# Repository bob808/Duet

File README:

# The Sweet Silence! 3D Printer Controller design files repository.

Sweeet Silence is a Duet2 Wifi spinoff, using tmc2228 drivers, mounted on the back of the pcb for better 
cooling (heatsinks on top pf pcb). Uses the same ATSAM4E8E processor. Output stage has been completely redone,
and includes full protection suite from the datasheet (ferrite beads/varistors and caps on BRA/BRB).
There's 2x MAX31865 chips on board, you can use it directly with PT100/1000 sensors. There's also options
for 4/3/2 wire setups.
The driver control should be the same from Maestro.
There's E2/E3 extra UART connections for external drivers.
Few pins from 2x25 header are different, and debugging led is gone. Everything else should be the same.

Will update later on with more details. I found all parts at TME/Farnell. 
Firmware needs to be modified to account for correct pin numbers.
Ah, and max31865 is to be bitbanged. No hardware SPI in that area.

The recommended firmware is DC42's branch of the RepRapFirmware:
https://github.com/dc42/RepRapFirmware

Based on :
Duet 2 Wifi 
Design by Tony Lock and David Crocker
More info:
https://www.duet3d.com/
LICENSE: see the LICENSE file in the repository

Developed in KiCAD: http://www.kicad-pcb.org/display/KICAD/KiCad+EDA+Software+Suite

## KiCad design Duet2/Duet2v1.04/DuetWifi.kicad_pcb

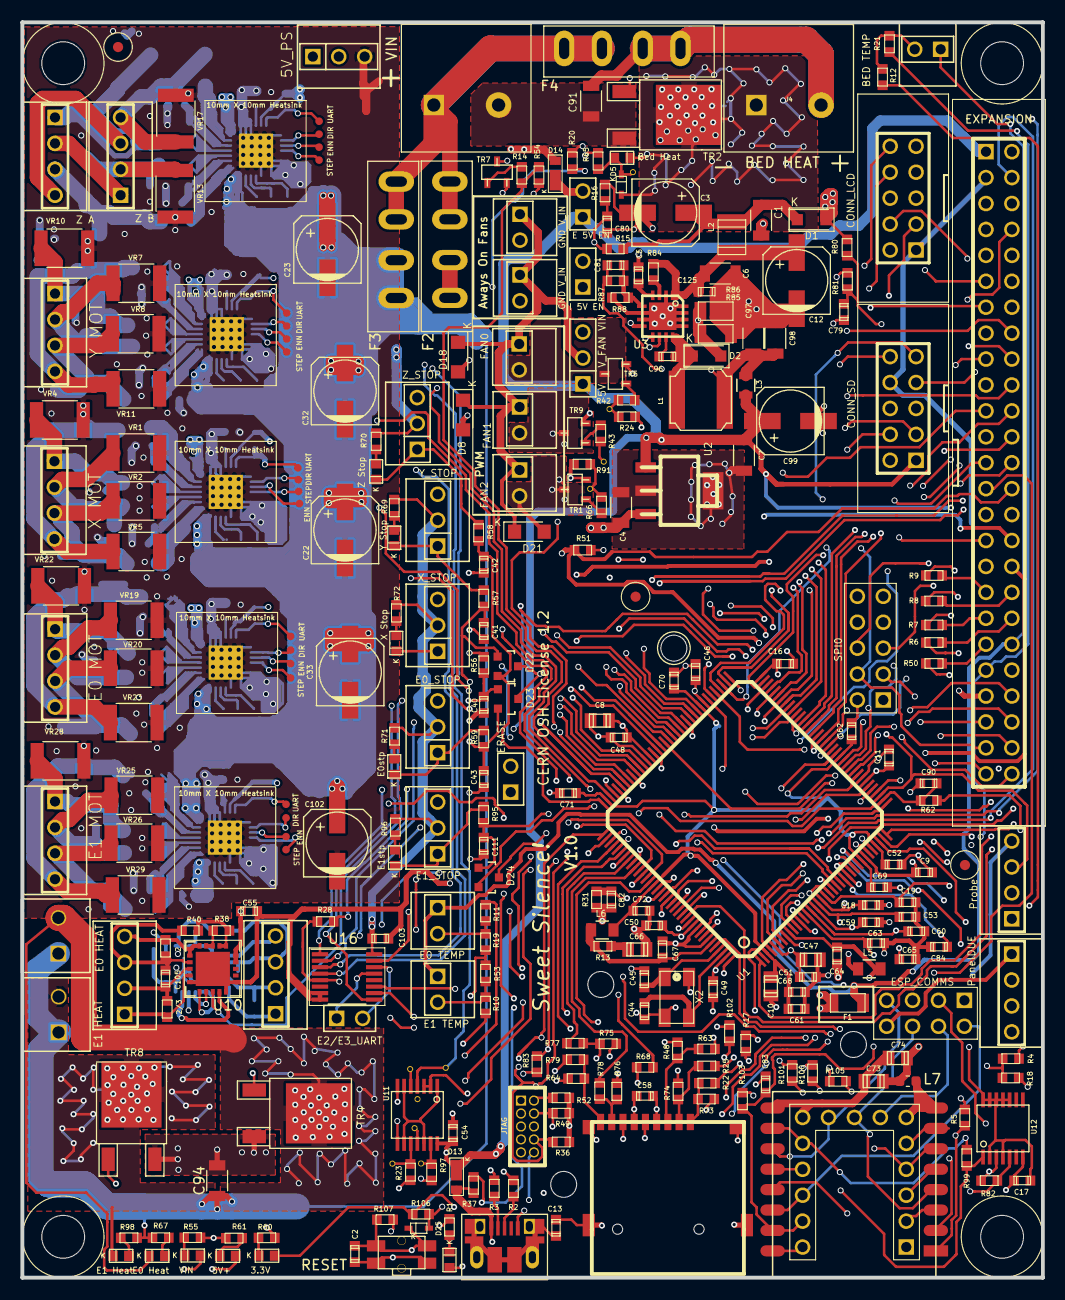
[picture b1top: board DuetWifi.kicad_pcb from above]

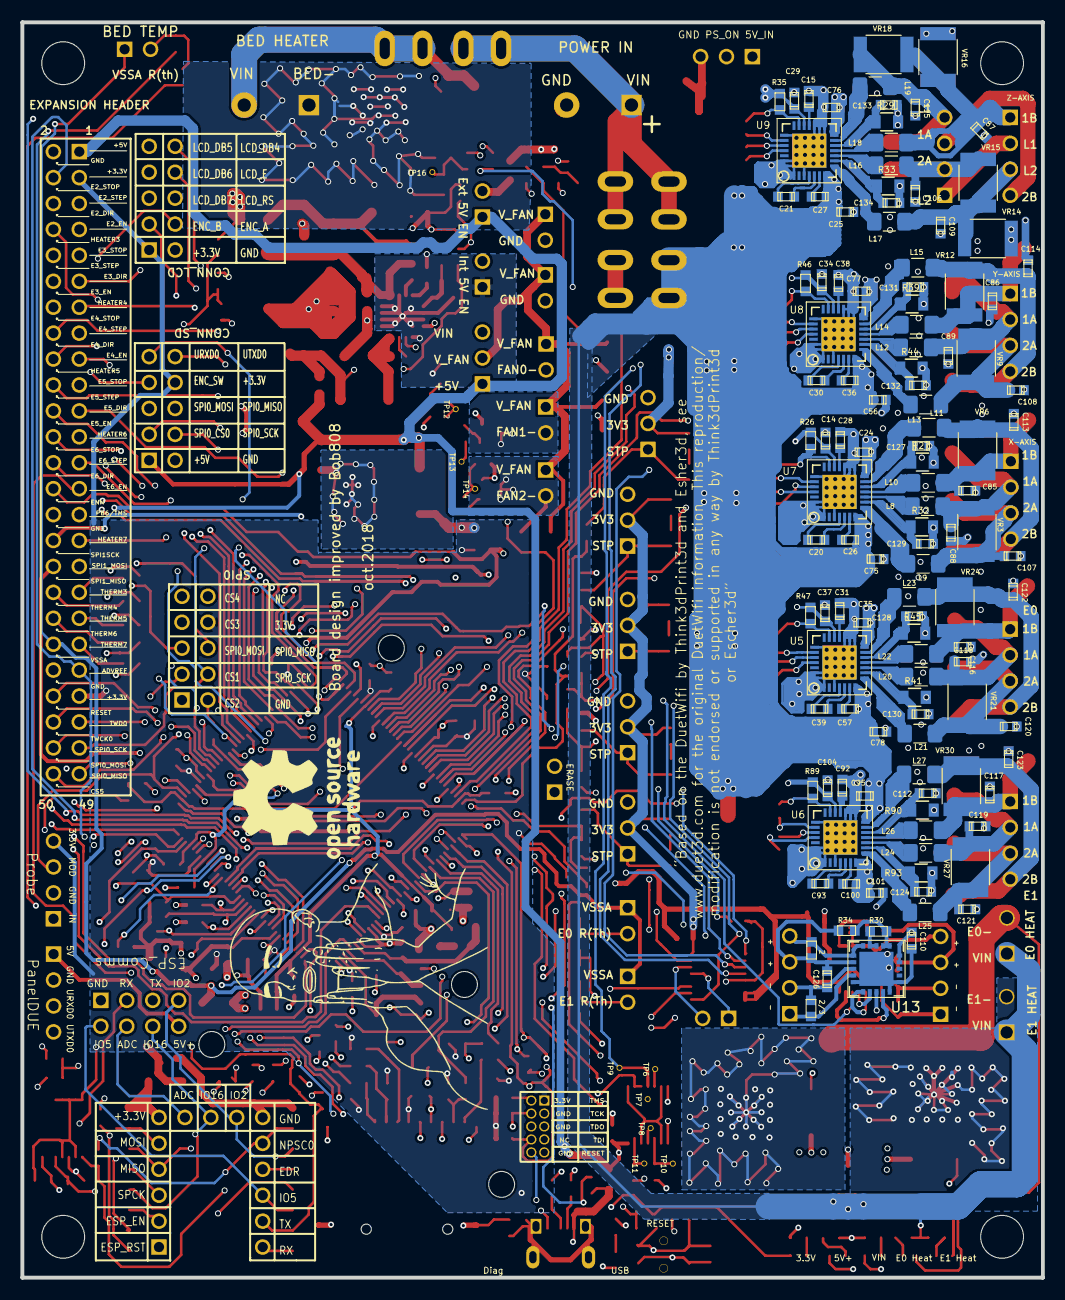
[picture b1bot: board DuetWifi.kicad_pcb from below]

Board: 4 copper layers, 100.0 x 123.0 mm, 430 parts (120 on the bottom side), 305 nets.

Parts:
C1, C4, C6, C7, C91, C94, C97, C98: 10u 35V; C_1206
C2, C13, C79, C80, C81: 0u01; C_0603
C3, C12, C22, C23, C32, C33, C102: 100u 35V; C_ELEC_6.3x7.7
C5, C9, C11, C16, C17, C29, C34, C37, C46, C48, C49, C50, C51, C52, C54, C61, C62, C64, C67, C69, C70, C71, C72, C82, C103, C104: 0u1; C_0603
C8, C10, C47, C73, C74: 10u; C_0805
C14, C24, C25, C35, C56, C75, C76, C77, C78, C95, C101: 0u1 50V; C_0603
C15, C18, C19, C28, C31, C38, C53, C58, C59, C60, C63, C65, C68, C84, C92: 2u2; C_0603
C20, C21, C30, C39, C93: 22n X7R 10% 16V; C_0603
C26, C27, C36, C57, C100: 0.1u 50V; C_0603
C40, C41, C42, C43, C55, C90, C110, C111: 2n2; C_0603
C44, C45: 10p; C_0603
C66: 4u7; C_0805
C83: DNP 47p; C_0603
C85, C86, C87, C88, C89, C106, C107, C108, C109, C113, C114, C115, C116, C117, C118, C119, C120, C121, C122, C123: 470p 100V; C_0603
C96: 22nF; C_0603
C99: 220u 25V; C_ELEC_6.3x7.7
C105, C126: 10n/100n; C_0603
C112, C124, C127, C128, C129, C130, C131, C132, C133, C134: 0u1 16V; C_0603
C125: 0u1 35V; C_0603
D1, D2: DB2W40300L; D_SOD-123F
D3: USB; D_0603
D5, D25: SOD-523F
D6: Bed Heat; D_0603
D7: E0 Heat; D_0603
D8, D18, D21: DO-219AB
D9: Y Stop; D_0603
D10: Z Stop; D_0603
D11: E0stp; D_0603
D12: X Stop; D_0603
D13, D14: SS14M; uSMA
D15: VIN; D_0603
D16: 3.3V; D_0603
D17: 5V+; D_0603
D19: E1stp; D_0603
D20: E1 Heat; D_0603
D22, D23, D24: BAT54C; SOT-23-D
F1: PPTC Resettable Fuse; R_1206
F2: FAN FUSE; MCCQ-122-minibladefuseholder
F3: EXT/STEP FUSE; MCCQ-122-minibladefuseholder
F4: BED FUSE; MCCQ-122-minibladefuseholder
J1: EXPANSION; PIN_ARRAY_25X2
J2: FAN2; PIN_ARRAY_2X1
J3: 5V V_FAN VIN; CONN_3x1
J4: BED HEAT; TERM_2-WAY_6.35mm
J5: BED TEMP; PIN_ARRAY_2X1
J6: E1 MOT; PIN_ARRAY_4x1
J7: Z B; PIN_ARRAY_4x1
J8: Y MOT; PIN_ARRAY_4x1
J9: X MOT; PIN_ARRAY_4x1
J10: E0 MOT; PIN_ARRAY_4x1
J11: E0 HEAT; 3.5MM_2X1
J12: E0 TEMP; PIN_ARRAY_2X1
J13: E1 HEAT; 3.5MM_2X1
J14: E1 TEMP; PIN_ARRAY_2X1
J15: uSDHC; uSD_SKT
J16: CONN_ALT_HEADER
J17, J18: + + - -; PIN_ARRAY_4x1
J19: Z_STOP; PIN_ARRAY_3X1
J20: 5V_PS; PIN_ARRAY_3X1
J21: JTAG; MICRO_5x2
J22: USB; uUSB_new
J23: VIN; TERM_2-WAY_6.35mm
J24, J31: GND V_IN; PIN_ARRAY_2X1
J25: FAN0; PIN_ARRAY_2X1
J26: E2/E3_UART; PIN_ARRAY_2X1_mod
J27, J42, J46, J50, J54: UART; tp_smd
J28: Probe; PIN_ARRAY_4x1
J29: FAN1; PIN_ARRAY_2X1
J30: PanelDUE; PIN_ARRAY_4x1
J32: Y_STOP; PIN_ARRAY_3X1
J33: X_STOP; PIN_ARRAY_3X1
J34: E0_STOP; PIN_ARRAY_3X1
J35: E1_STOP; PIN_ARRAY_3X1
J36: Z A; PIN_ARRAY_4x1
J37: SPI0; MAX_TEMP_DB
J38, J43, J47, J51, J55: ENN; tp_smd
J39: ESP_COMMS; CONN_4x2
J40, J44, J48, J52, J56: DIR; tp_smd
J41, J45, J49, J53, J57: STEP; tp_smd
JP1: ERASE; JUMPER
JP9: I 5V EN; JUMPER
JP10: E 5V EN; JUMPER
Ju1, Ju4: 2; R_0603
Ju2, Ju3: 2/3; R_0603
L1: 10uH; L_6x6
L2: 1uH; C_1210
L3: 220 ohm, 3 A; R_0805
L5, L6: 10uH 100Mhz; R_0805_extended_pads
L7: 4n7h; L_0603_1608Metric
L8, L10, L11: 50R@100MHz; L_1206_3216Metric_Pad1.42x1.75mm_HandSolder
L9, L12, L13, L14, L15, L16, L17, L18, L19, L20, L21, L22, L23, L24, L25, L26, L27: 50R@100MHz; R_1206_3216Metric_Pad1.42x1.75mm_HandSolder
M1, M2, M3: FID; Fiducial_1mm_Dia_2.54mm_Outer_CopperTop
M4, M5, M6, M7: MOUNTING; Fixing_M4
M8: LOGO; LOGO1
M11: LOGO; Untitled
P1: CONN_SD; IDC_PIN_ARRAY_5x2
P2: CONN_LCD; IDC_PIN_ARRAY_5x2
R1, R4, R17, R61, R99, R102: 2K2; R_0603
R2, R3: 27R 1%; R_0603
R5, R103: 470R; R_0603
R6, R7, R8, R9, R10, R11, R12, R24, R50, R51, R56, R57, R58, R59, R62, R63, R64, R83, R91, R95, R106: 10K; R_0603
R13: 1R; R_0603
R14, R28, R42, R43, R66, R69, R70, R71, R72, R96: 1K; R_0603
R15, R80: 47K 1%; R_0603
R16, R81: 4K7 1%; R_0603
R18, R54, R55, R65, R67, R98: 4K7; R_0603
R19, R21, R53: 4K7 0.1%; R_0603
R20, R23, R60, R97: 180R; R_0603
R22, R25, R48, R77, R78, R79: 220R; R_0603
R26, R35, R46, R47, R89: 22K; R_0603
R27, R29, R32, R33, R39, R41, R44, R45, R90, R93: 0R075 1% 0.33W; R_0805_extended_pads
R30, R38: 3k9; R_0603
R31: 47K; R_0603
R34, R40: 10M; R_0603
R36, R49, R52: DNP 100K; R_0603
R37: 27K; R_0603
R68, R107: 100R; R_0603
R73, R74, R75, R76: DNP 47K; R_0603
R82: 0R DNP; R_0603
R84: 100K; R_0603
R85, R86: 0R13 0.33W; R_1206
R87: 3K6; R_0603
R88: 680R; R_0603
R100, R101, R105: 47R; R_0603
S1: RESET; SW_SIDE_1_lugs
TP6, TP7, TP8, TP9, TP10, TP11, TP12, TP13, TP14, TP16: TP; TP_via
TR1, TR5, TR7, TR9: PMV40UN2; SOT-23
TR2, TR4, TR8: IPD036N04L; D-PAK
U1: ATSAM4E8E; LQFP144
U2: AP7361C-33E-13; SOT-223
U3: A4403; QFN16-4x4
U4: ESP-07/12; ESP-12S
U5, U6, U7, U8, U9: TMC2224; QFN-28-1EP_5x5mm_Pitch0.5mm
U10, U13: MAX31865AAP(SSOP20); QFN-20-1EP_5x5mm_Pitch0.65mm_mod
U11: 74HCT02; TSSOP-14
U12: 74HC74; TSSOP-14
U16: SN74CB3Q3251; QSOP-16_3.9x4.9mm_Pitch0.635mm
VR1, VR2, VR3, VR4, VR5, VR6, VR7, VR8, VR9, VR10, VR11, VR12, VR13, VR14, VR15, VR16, VR17, VR18, VR19, VR20, VR21, VR22, VR23, VR24, VR25, VR26, VR27, VR28, VR29, VR30: 3J; L_1812_HandSoldering
X2: CRYSTAL_4PIN; Xtal_5x3.2

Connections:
5V_IN: D14.1, J20.1
+3.3V: C4.1, C8.1, C9.1, C11.1, C14.1, C16.1, C17.1, C29.1, C34.1, C37.1, C46.1, C47.1, C48.1, C49.1, C50.1, C51.1, C55.1, C58.1, C73.1, C74.1, C103.2, C104.1, C110.1, D16.1, D22.3, D23.3, D24.3, J1.3, J1.43, J15.4, J19.2, J21.1, J28.4, J32.2, J33.2, J34.2, J35.2, J37.8, JP1.1, L5.2, L7.1, P1.8, P2.1, R26.2, R35.2, R36.1, R46.2, R47.2, R49.1, R51.1, R52.1, R63.2, R64.2, R69.2, R70.2, R71.2, R72.2, R73.2, R74.2, R75.2, R76.2, R89.1, R96.2, R106.2, U1.5, U1.30, U1.43, U1.72, U1.80, U1.96, U1.134, U1.143, U2.3, U5.19, U6.19, U7.19, U8.19, U9.19, U10.19, U10.20, U11.2, U11.3, U12.2, U12.4, U12.10, U12.11, U12.12, U12.13, U12.14, U13.19, U13.20, U16.16
+5V: C7.1, C54.1, C99.1, D13.2, D17.1, J1.1, J1.33, J3.1, J30.1, J39.8, JP10.1, L3.1, P1.1, U2.1, U11.14
/Processor/VDDCORE: C10.1, C52.1, C61.1, C62.1, C68.1, C69.1, C70.1, C71.1, C72.1, L6.1, U1.3, U1.29, U1.33, U1.50, U1.81, U1.107, U1.123
ADC: J16.7, J39.4, U4.2
ADVREF: C64.1, J1.41, L5.1, R19.2, R21.2, R53.2, U1.9
BED-: D5.2, D6.2, J4.1, TR2.D
BED_PWM: R20.2, TP9.1, U11.4
CS3: J37.7, U1.117
CS4: J37.9, U1.120
CS5: J1.50, U1.56
D6_TestPoint: D5.1, D6.1, R65.1, TP16.1
DDM: R3.2, U1.136
DDP: R2.2, U1.137
E0-: D7.2, J11.2, TR4.D
E0_DIR: J52.1, U1.99, U5.23
E0_MOT_1A: C118.1, J10.2, L20.1, VR19.1, VR21.1
E0_MOT_1B: C116.1, J10.1, L22.1, VR22.1, VR24.1
E0_MOT_2A: C120.2, J10.3, L21.1, VR20.2, VR21.2
E0_MOT_2B: C122.2, J10.4, L23.1, VR23.2, VR24.2
E0_PWM: R23.2, TP10.1, U11.10
E0_STEP: J53.1, U1.125, U5.25
E0_STOP: C43.1, D23.2, R59.1, U1.101
E0_STOP_CONN: D11.2, J34.1, R59.2
E0_UART: J50.1, R47.1, U5.20, U16.1
E1-: D20.2, J13.2, TR8.D
E1_DIR: J56.1, U1.110, U6.23
E1_MOT_1A: C119.1, J6.2, L24.1, VR25.1, VR27.1
E1_MOT_1B: C117.1, J6.1, L26.1, VR28.1, VR30.1
E1_MOT_2A: C121.2, J6.3, L25.1, VR26.2, VR27.2
E1_MOT_2B: C123.2, J6.4, L27.1, VR29.2, VR30.2
E1_PWM: R97.2, TP11.1, U11.13
E1_STEP: J57.1, U1.126, U6.25
E1_STOP: C111.1, D24.1, R95.1, U1.100
E1_STOP_CONN: D19.2, J35.1, R95.2
E1_UART: J54.1, R89.2, U6.20, U16.15
E2_DIR: J1.6, U1.71
E2_EN: J1.7, U1.57
E2_STEP: J1.5, U1.131
E2_STOP: J1.4, U1.4
E2_UART: J26.2, U16.14
E3_DIR: J1.11, U1.60
E3_EN: J1.12, U1.55
E3_STEP: J1.10, U1.132
E3_STOP: J1.9, U1.6
E3_UART: J26.1, U16.13
E4_DIR: J1.16, U1.78
E4_EN: J1.17, U1.52
E4_STEP: J1.15, U1.1
E4_STOP: J1.14, U1.7
E5_DIR: J1.21, U1.74
E5_EN: J1.22, U1.53
E5_STEP: J1.20, U1.128
E5_STOP: J1.19, U1.10
E6_DIR: J1.26, U1.11
E6_EN: J1.27, U1.140
E6_STEP: J1.25, U1.47
E6_STOP: J1.24, U1.25
EDR_CONN: J16.12, R17.1, U4.12
ENC_A: P2.4, U1.36
ENC_B: P2.3, U1.48
ENC_SW: P1.7, U1.35
ENN: J1.28, J38.1, J43.1, J47.1, J51.1, J55.1, R51.2, U1.54, U5.24, U6.24, U7.24, U8.24, U9.24
ERASE: JP1.2, U1.87
ESP_3.3VIN: J16.6, L7.2, U4.8
ESP_DATA_RDY: R17.2, U1.2
ESP_EN: J16.2, R18.1, U1.28, U4.3
ESP_RST: J16.1, R5.2, U1.27
FAN0: R24.2, R42.2, TP12.1, U1.127
FAN0-: D18.2, J25.2, TR5.D
FAN1: R43.2, TP13.1, U1.13
FAN1-: D8.2, J29.2, TR9.D
FAN2: R66.2, R91.2, TP14.1, U1.102
FAN2-: D21.2, J2.2, TR1.D
GND: C1.2, C2.2, C3.2, C4.2, C5.2, C6.2, C7.2, C8.2, C9.2, C10.2, C11.2, C12.2, C13.2, C14.2, C15.2, C16.2, C17.2, C18.2, C19.2, C22.2, C23.2, C24.2, C25.2, C28.2, C29.2, C31.1, C32.2, C33.2, C34.2, C35.2, C37.2, C38.2, C40.2, C41.2, C42.2, C43.2, C44.2, C45.2, C46.2, C47.2, C48.2, C49.2, C50.2, C51.2, C52.2, C53.2, C54.2, C55.2, C56.2, C58.2, C59.2, C60.2, C61.2, C62.2, C63.2, C64.2, C65.2, C66.2, C67.2, C68.2, C69.2, C70.2, C71.2, C72.2, C73.2, C74.2, C75.2, C76.2, C77.2, C78.2, C79.2, C80.2, C82.2, C83.2, C84.2, C85.1, C86.1, C87.1, C88.1, C89.1, C90.2, C91.2, C92.2, C94.2, C95.2, C97.2, C98.2, C99.2, C101.2, C102.2, C103.1, C104.2, C106.1, C107.2, C108.2, C109.2, C110.2, C111.2, C112.1, C113.2, C114.2, C115.2, C116.2, C117.2, C118.2, C119.2, C120.1, C121.1, C122.1, C123.1, C124.1, C125.2, C127.1, C128.1, C129.1, C130.1, C131.1, C132.1, C133.1, C134.1, F1.2, J1.2, J1.30, J1.42, J15.6, J15.G, J16.10, J19.3, J20.3, J21.3, J21.5, J21.9, J22.5, J23.2, J24.2, J28.2, J30.2, J31.2, J32.3, J33.3, J34.3, J35.3, J37.2, J39.1, JP9.1, P1.2, P2.2, R1.2, R4.2, R16.2, R18.2, R24.1, R27.1, R29.1, R31.2, R32.1, R33.1, R39.1, R41.1, R44.1, R45.1, R54.2, R55.2, R60.2, R61.2, R81.2, R85.1, R86.1, R88.2, R90.2, R91.1, R93.2, S1.1, S1.2, TR1.S, TR2.S, TR4.S, TR5.S, TR7.S, TR8.S, TR9.S, U1.8, U1.44, U1.61, U1.85, U1.95, U1.104, U1.115, U1.135, U1.138, U2.2, U2.4, U3.2, U3.6, U3.7, U3.9, U3.13, U3.14, U3.15, U3.16, U3.17, U4.9, U5.1, U5.3, U5.15, U5.16, U5.17, U5.22, U5.27, U5.28, U5.29, U6.1, U6.3, U6.15, U6.16, U6.17, U6.22, U6.27, U6.28, U6.29, U7.1, U7.3, U7.15, U7.16, U7.17, U7.22, U7.27, U7.28, U7.29, U8.1, U8.3, U8.15, U8.16, U8.17, U8.22, U8.27, U8.28, U8.29, U9.1, U9.3, U9.15, U9.16, U9.17, U9.22, U9.27, U9.28, U9.29, U10.10, U10.15, U10.16, U10.21, U11.7, U12.7, U13.10, U13.15, U13.16, U13.21, U16.7, U16.8, VR1.2, VR2.1, VR4.2, VR5.1, VR7.2, VR8.1, VR10.2, VR11.1, VR13.2, VR14.1, VR16.2, VR17.1, VR19.2, VR20.1, VR22.2, VR23.1, VR25.2, VR26.1, VR28.2, VR29.1, X2.2, X2.4
GPIO2: J16.9, J39.7, U4.11
GPIO5: J16.13, J39.2, U4.14
GPIO16: J16.8, J39.6, U4.4
HEATER0: TP6.1, U1.23, U11.5
HEATER1: TP7.1, U1.22, U11.8
HEATER2: TP8.1, U1.45, U11.11
HEATER3: J1.8, U1.40
HEATER4: J1.13, U1.58
HEATER5: J1.18, U1.82
HEATER6: J1.23, U1.94
HEATER7: J1.31, U1.49
LCD_DB4: P2.10, U1.63
LCD_DB5: P2.9, U1.65
LCD_DB6: P2.7, U1.67
LCD_DB7: P2.5, U1.69
LCD_E: P2.8, U1.59
LCD_RS: P2.6, U1.76
MCCDA: R48.2, U1.112
MCCK: R68.2, U1.129
MCDA0: R77.2, U1.116
MCDA1: R78.2, U1.118
MCDA2: R22.2, U1.62
MCDA3: R25.2, U1.70
MISO: R101.2, U1.68
MISO_ESP: J16.4, R101.1, U4.6
MOSI: R105.2, U1.42
MOSI_ESP: J16.5, R105.1, U4.7
MOT_RXD: J1.34, R28.1, U1.32, U16.5
MOT_TXD: J1.32, R28.2, U1.37
MUX_0: U1.133, U16.11
MUX_1: J21.6, U1.109, U16.10
MUX_2: U1.86, U16.9
NPCS0: R99.2, U1.64, U12.1
NPCS0_CONN: J16.11, R99.1, U4.10
unnamed: C1.1, C3.1, D1.1, L2.2, R15.1
unnamed: C2.1, D25.1, R107.1, S1.3, S1.4
unnamed: C5.1, U3.4
unnamed: C6.1, C12.1, C125.1, L2.1, R84.1, U3.1
unnamed: C13.1, J22.CE
unnamed: C15.1, U9.18
unnamed: C18.1, R11.2, U1.18
unnamed: C19.1, R12.2, U1.19
unnamed: C20.1, U7.5
unnamed: C20.2, U7.4
unnamed: C21.1, U9.5
unnamed: C21.2, U9.4
unnamed: C26.2, U7.6
unnamed: C27.2, U9.6
unnamed: C28.1, U7.18
unnamed: C30.1, U8.5
unnamed: C30.2, U8.4
unnamed: C31.2, U5.18
unnamed: C36.2, U8.6
unnamed: C38.1, U8.18
unnamed: C39.1, U5.5
unnamed: C39.2, U5.4
unnamed: C44.1, U1.142, X2.3
unnamed: C45.1, U1.141, X2.1
unnamed: C53.1, R10.2, U1.17
unnamed: C57.2, U5.6
unnamed: C59.1, R9.2, U1.16
unnamed: C60.1, R8.2, U1.15
unnamed: C63.1, R7.2, U1.14
unnamed: C65.1, R6.2, U1.12
unnamed: C66.1, R13.2
unnamed: C67.1, L6.2, R13.1, U1.139
unnamed: C81.1, C97.1, C98.1, L1.1, L3.2, R87.1
unnamed: C81.2, R87.2, R88.1, U3.5
unnamed: C84.1, R50.2, U1.24
unnamed: C92.1, U6.18
unnamed: C93.1, U6.4
unnamed: C93.2, U6.5
unnamed: C96.1, U3.11
unnamed: C96.2, D2.1, L1.2, U3.12
unnamed: C100.2, U6.6
unnamed: C105.1, J17.2, Ju2.2, U10.8
unnamed: C105.2, J17.3, Ju1.1, R40.2, U10.7
unnamed: C112.2, R90.1, U6.12
unnamed: C124.2, R93.1, U6.9
unnamed: C126.1, J18.2, Ju3.1, U13.8
unnamed: C126.2, J18.3, Ju4.1, R34.2, U13.7
unnamed: C127.2, R27.2, U7.12
unnamed: C128.2, R45.2, U5.12
unnamed: C129.2, R32.2, U7.9
unnamed: C130.2, R41.2, U5.9
unnamed: C131.2, R39.2, U8.12
unnamed: C132.2, R44.2, U8.9
unnamed: C133.2, R29.2, U9.12
unnamed: C134.2, R33.2, U9.9
unnamed: D2.2, R85.2, R86.2, U3.8
unnamed: D3.2, R1.1
unnamed: D7.1, R67.1
unnamed: D9.1, R69.1
unnamed: D10.1, R70.1
unnamed: D11.1, R71.1
unnamed: D12.1, R72.1
unnamed: D14.2, JP10.2
unnamed: D15.2, R55.1
unnamed: D16.2, R60.1
unnamed: D17.2, R61.1
unnamed: D19.1, R96.1
unnamed: D20.1, R98.1
unnamed: F2.2, J3.3
unnamed: J15.1, R22.1, R73.1
unnamed: J15.2, R25.1, R74.1
unnamed: J15.3, R48.1, R63.1
unnamed: J15.5, R68.1
unnamed: J15.7, R75.1, R77.1
unnamed: J15.8, R76.1, R78.1
unnamed: J15.9, R64.1, R79.1
unnamed: J17.1, Ju2.1, U10.9
unnamed: J17.4, Ju1.2, U10.5, U10.6
unnamed: J18.1, Ju3.2, U13.9
unnamed: J18.4, Ju4.2, U13.5, U13.6
unnamed: J22.2, R3.1
unnamed: J22.3, R2.1
unnamed: J7.1, J36.2
unnamed: J7.3, J36.4
unnamed: JP9.2, U3.10
unnamed: L8.2, U7.10
unnamed: L9.2, U7.8
unnamed: L10.2, U7.11
unnamed: L11.2, U7.13
unnamed: L12.2, U8.10
unnamed: L13.2, U8.8
unnamed: L14.2, U8.11
unnamed: L15.2, U8.13
unnamed: L16.2, U9.10
unnamed: L17.2, U9.8
unnamed: L18.2, U9.11
unnamed: L19.2, U9.13
unnamed: L20.2, U5.10
unnamed: L21.2, U5.8
unnamed: L22.2, U5.11
unnamed: L23.2, U5.13
unnamed: L24.2, U6.10
unnamed: L25.2, U6.8
unnamed: L26.2, U6.11
unnamed: L27.2, U6.13
unnamed: R4.1, R5.1, U4.1
unnamed: R14.1, TR7.G
unnamed: R20.1, TR2.G
unnamed: R23.1, TR4.G
unnamed: R30.1, R34.1, U13.1, U13.2
unnamed: R30.2, U13.3, U13.4
unnamed: R38.1, R40.1, U10.1, U10.2
unnamed: R38.2, U10.3, U10.4
unnamed: R42.1, TR5.G
unnamed: R43.1, TR9.G
unnamed: R66.1, TR1.G
unnamed: R82.2, U4.13, U12.5
unnamed: R84.2, U3.3
unnamed: R97.1, TR8.G
unnamed: U11.1, U11.6, U11.9, U11.12
PB6/TMS: J1.29, J21.2, R52.2, U1.79
PB7/TCK: J21.4, R49.2, R83.2, U1.89
PS_ON: R14.2, R54.1, U1.106
PS_ON_IN: J20.2, TR7.D
PWR_FAIL_DET1: C80.1, R15.2, R16.1, U1.31
PWR_FAIL_DET2: C79.1, R80.2, R81.1, U1.41
RESET: D25.2, J21.10, R106.1, U1.83
RESET_EXT: J1.44, R107.2
SAM_TFR_RDY: R82.1, U1.34, U12.3
SD_CD: R79.2, U1.122
SPCK: R100.2, U1.51
SPCK_ESP: J16.3, R100.1, U4.5
SPI0_CS0: P1.3, U1.130
SPI0_CS1: J37.3, U1.26
SPI0_CS2: J37.1, U1.111
SPI0_MISO: J1.49, J37.6, P1.6, U1.21
SPI0_MOSI: J1.48, J37.5, P1.5, U1.20
SPI0_SCK: J1.47, J37.4, P1.4, U1.144
TEMP_CS1: U1.84, U10.13
TEMP_CS2: J21.8, R36.2, U1.105, U13.13
TEMP_MISO: U1.103, U10.14, U13.14
TEMP_MOSI: U1.90, U10.11, U13.11
TEMP_SCK: U1.46, U10.12, U13.12
THERMISTOR0: J5.2, R12.1, R21.1
THERMISTOR1: J12.2, R11.1, R19.1
THERMISTOR2: J14.2, R10.1, R53.1
THERMISTOR3: J1.35, R9.1
THERMISTOR4: J1.36, R8.1
THERMISTOR5: J1.37, R7.1
THERMISTOR6: J1.38, R6.1
THERMISTOR7: J1.39, R50.1
TWCK0: J1.46, U1.77
TWD0: J1.45, U1.91
URXD0: J30.3, P1.9, U1.75
URXD1: R102.2, U1.73
URXD1_CONN: J16.15, J39.3, R102.1, U4.16
USB_PWR_MON: C82.1, R31.1, R37.2, U1.124
UTXD0: J30.4, P1.10, U1.66
UTXD1: R103.2, U1.114
UTXD1_CONN: C83.1, J16.14, J39.5, R103.1, U4.15
VBUS: D3.1, D13.1, J22.1, R37.1
VSSA: F1.1, J1.40, J5.1, J12.1, J14.1, R83.1
V_BED: C91.1, F4.2, J4.2, R65.2
V_FAN: D8.1, D18.1, D21.1, J2.1, J3.2, J24.1, J25.1, J29.1, J31.1
V_FUSED: C22.1, C23.1, C24.1, C25.1, C26.1, C27.1, C32.1, C33.1, C35.1, C36.1, C56.1, C57.1, C75.1, C76.1, C77.1, C78.1, C94.1, C95.1, C100.1, C101.1, C102.1, D1.2, F3.2, J11.1, J13.1, R67.2, R80.1, R98.2, U5.7, U5.14, U6.7, U6.14, U7.7, U7.14, U8.7, U8.14, U9.7, U9.14
V_IN: D15.1, F2.1, F3.1, F4.1, J23.1
X_DIR: J40.1, U1.98, U7.23
X_MOT_1A: C88.2, J9.2, L8.1, VR1.1, VR3.1
X_MOT_1B: C85.2, J9.1, L10.1, VR4.1, VR6.1
X_MOT_2A: C107.1, J9.3, L9.1, VR2.2, VR3.2
X_MOT_2B: C113.1, J9.4, L11.1, VR5.2, VR6.2
X_STEP: J41.1, U1.121, U7.25
X_STOP: C40.1, D23.1, R56.1, U1.97
X_STOP_CONN: D12.2, J33.1, R56.2
X_UART: J27.1, R26.1, U7.20, U16.2
Y_DIR: J44.1, U1.92, U8.23
Y_MOT_1A: C89.2, J8.2, L12.1, VR7.1, VR9.1
Y_MOT_1B: C86.2, J8.1, L14.1, VR10.1, VR12.1
Y_MOT_2A: C108.1, J8.3, L13.1, VR8.2, VR9.2
Y_MOT_2B: C114.1, J8.4, L15.1, VR11.2, VR12.2
Y_STEP: J45.1, U1.119, U8.25
Y_STOP: C41.1, D22.1, R57.1, U1.93
Y_STOP_CONN: D9.2, J32.1, R57.2
Y_UART: J42.1, R46.1, U8.20, U16.3
Z_DIR: J48.1, U1.88, U9.23
Z_MOT_1A: C106.2, J7.2, L16.1, VR13.1, VR15.1
Z_MOT_1B: C87.2, J36.1, L18.1, VR16.1, VR18.1
Z_MOT_2A: C109.1, J36.3, L17.1, VR14.2, VR15.2
Z_MOT_2B: C115.1, J7.4, L19.1, VR17.2, VR18.2
Z_PROBE_IN: J28.1, R62.2
Z_PROBE_MCU: C90.1, D24.2, R62.1, U1.38
Z_PROBE_MOD: J28.3, U1.39
Z_STEP: J49.1, U1.113, U9.25
Z_STOP: C42.1, D22.2, R58.1, U1.108
Z_STOP_CONN: D10.2, J19.1, R58.2
Z_UART: J46.1, R35.1, U9.20, U16.4

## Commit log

2018-10-30 cleaned up files
2018-10-30 fixed DRC
    FIxed DRC errors.
2018-10-30 images
2018-10-30 Rename README to README.md
2018-10-30 Update LICENSE
2018-11-01 added bom list.
    parts are spread among both vendors. you need the parts from both lists.
